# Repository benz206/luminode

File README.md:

# Luminode – WS2812B LED Controller (Rust + systemd)

This project runs a **WS2812B LED animation** on a **Raspberry Pi** using **Rust**, with **automatic startup on boot via systemd**.

It’s one compiled binary:

- no Python / venv
- no runtime dependencies
- no Cargo at boot

## Key properties

- Native Rust binary (low CPU usage)
- Uses PWM + DMA (GPIO 18)
- Stable WS2812B timing
- Auto-starts on boot
- Clean start / stop / restart workflow via systemd

## Project layout

Rust project:

```
~/luminode/
├── Cargo.toml
├── Cargo.lock
├── src/
│   └── main.rs
└── target/
    └── release/
        └── leds
```

Installed binary:

```
/usr/local/bin/leds
```

systemd service:

```
/etc/systemd/system/leds.service
```

## 1) Build the Rust binary

```bash
cd ~/luminode
cargo build --release
```

Output:

```
~/luminode/target/release/leds
```

## 2) Test the binary manually

WS2812B access requires root:

```bash
sudo ~/luminode/target/release/leds
```

Stop with `Ctrl+C`.

## 3) Install the binary system-wide

```bash
sudo cp ~/luminode/target/release/leds /usr/local/bin/leds
sudo chmod +x /usr/local/bin/leds
```

Test:

```bash
sudo /usr/local/bin/leds
```

## 4) Create the systemd service

Create:

```bash
sudo nano /etc/systemd/system/leds.service
```

Paste:

```ini
[Unit]
Description=WS2812B LED Controller (Rust)
After=multi-user.target

[Service]
Type=simple
User=root
ExecStart=/usr/local/bin/leds
Restart=always
RestartSec=2
Nice=10

[Install]
WantedBy=multi-user.target
```

## 5) Enable and start on boot

```bash
sudo systemctl daemon-reload
sudo systemctl enable leds.service
sudo systemctl start leds.service
```

Status:

```bash
sudo systemctl status leds.service
```

Logs:

```bash
journalctl -u leds.service -f
```

## Updating the Rust code

```bash
cd ~/luminode
cargo build --release
sudo cp target/release/leds /usr/local/bin/leds
sudo systemctl restart leds.service
```

## License

GNU General Public License v3.0

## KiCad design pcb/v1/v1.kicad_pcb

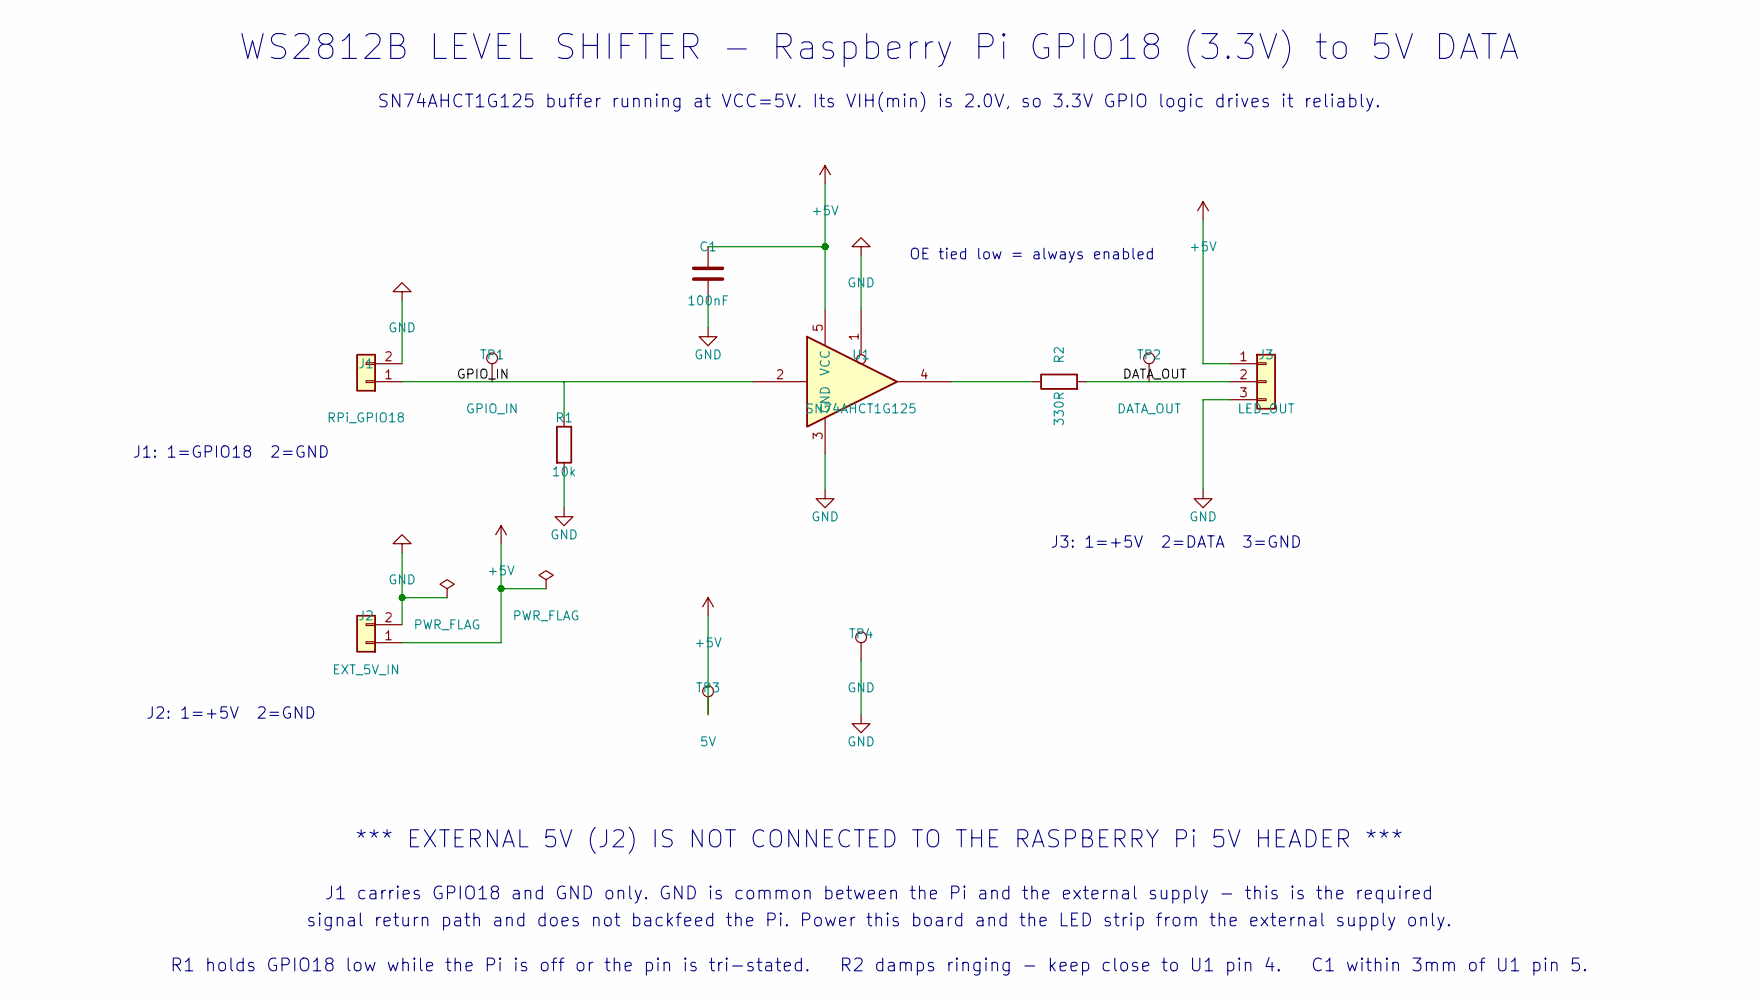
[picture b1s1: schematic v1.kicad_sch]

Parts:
C1: 100nF; C_0402_1005Metric
J1: RPi_GPIO18; PinHeader_1x02_P2.54mm_Vertical
J2: EXT_5V_IN; PinHeader_1x02_P2.54mm_Vertical
J3: LED_OUT; PinHeader_1x03_P2.54mm_Vertical
R1: 10k; R_0402_1005Metric
R2: 330R; R_0402_1005Metric
TP1: GPIO_IN; TestPoint_Pad_D1.5mm
TP2: DATA_OUT; TestPoint_Pad_D1.5mm
TP3: 5V; TestPoint_Pad_D1.5mm
TP4: GND; TestPoint_Pad_D1.5mm
U1: SN74AHCT1G125; SOT-23-5

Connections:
+5V: C1.1, J2.1, J3.1, TP3.1 (1_1), U1.5 (VCC)
/DATA_OUT: J3.2, R2.2, TP2.1 (1_1)
/GPIO_IN: J1.1, R1.1, TP1.1 (1_1), U1.2
GND: C1.2, J1.2, J2.2, J3.3, R1.2, TP4.1 (1_1), U1.1, U1.3 (GND)
unnamed: R2.1, U1.4

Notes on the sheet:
J1: 1=GPIO18 2=GND
J2: 1=+5V 2=GND
J3: 1=+5V 2=DATA 3=GND
WS2812B LEVEL SHIFTER - Raspberry Pi GPIO18 (3.3V) to 5V DATA
SN74AHCT1G125 buffer running at VCC=5V. Its VIH(min) is 2.0V, so 3.3V GPIO logic drives it reliably.
*** EXTERNAL 5V (J2) IS NOT CONNECTED TO THE RASPBERRY Pi 5V HEADER ***
J1 carries GPIO18 and GND only. GND is common between the Pi and the external supply - this is the required
signal return path and does not backfeed the Pi. Power this board and the LED strip from the external supply only.
R1 holds GPIO18 low while the Pi is off or the pin is tri-stated. R2 damps ringing - keep close to U1 pin 4. C1 within 3mm of U1 pin 5.
OE tied low = always enabled

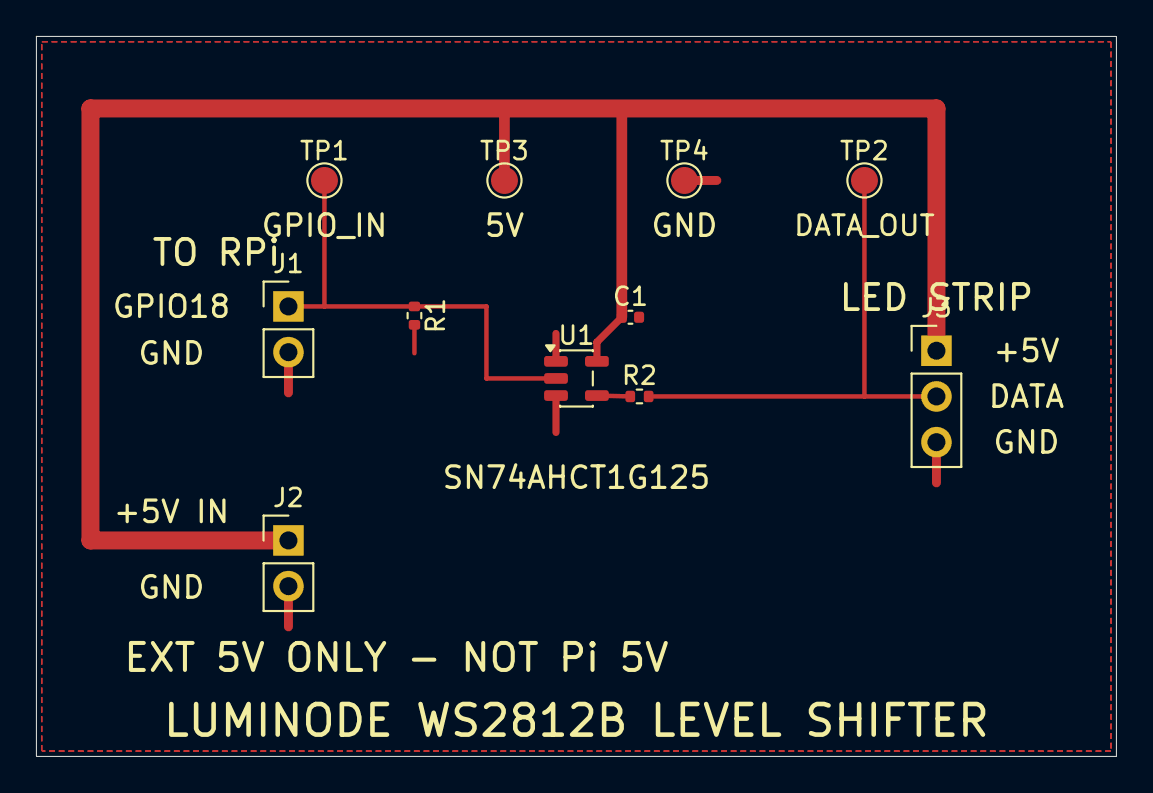
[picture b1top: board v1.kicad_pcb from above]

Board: 2 copper layers, 60.0 x 40.0 mm, 11 parts (0 on the bottom side), 5 nets.

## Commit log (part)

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2025-11-02 Add some reqs
2025-12-29 Add kicad
2026-01-12 ADD rpi prop
2026-01-13 Move
2026-01-13 Push
2026-01-13 Fix versions
2026-01-13 Smooth
2026-01-13 Fix readme
2026-01-13 Smoothen out
2026-04-10 Use serde into reader
2026-04-10 Finish
2026-04-10 Simplify
